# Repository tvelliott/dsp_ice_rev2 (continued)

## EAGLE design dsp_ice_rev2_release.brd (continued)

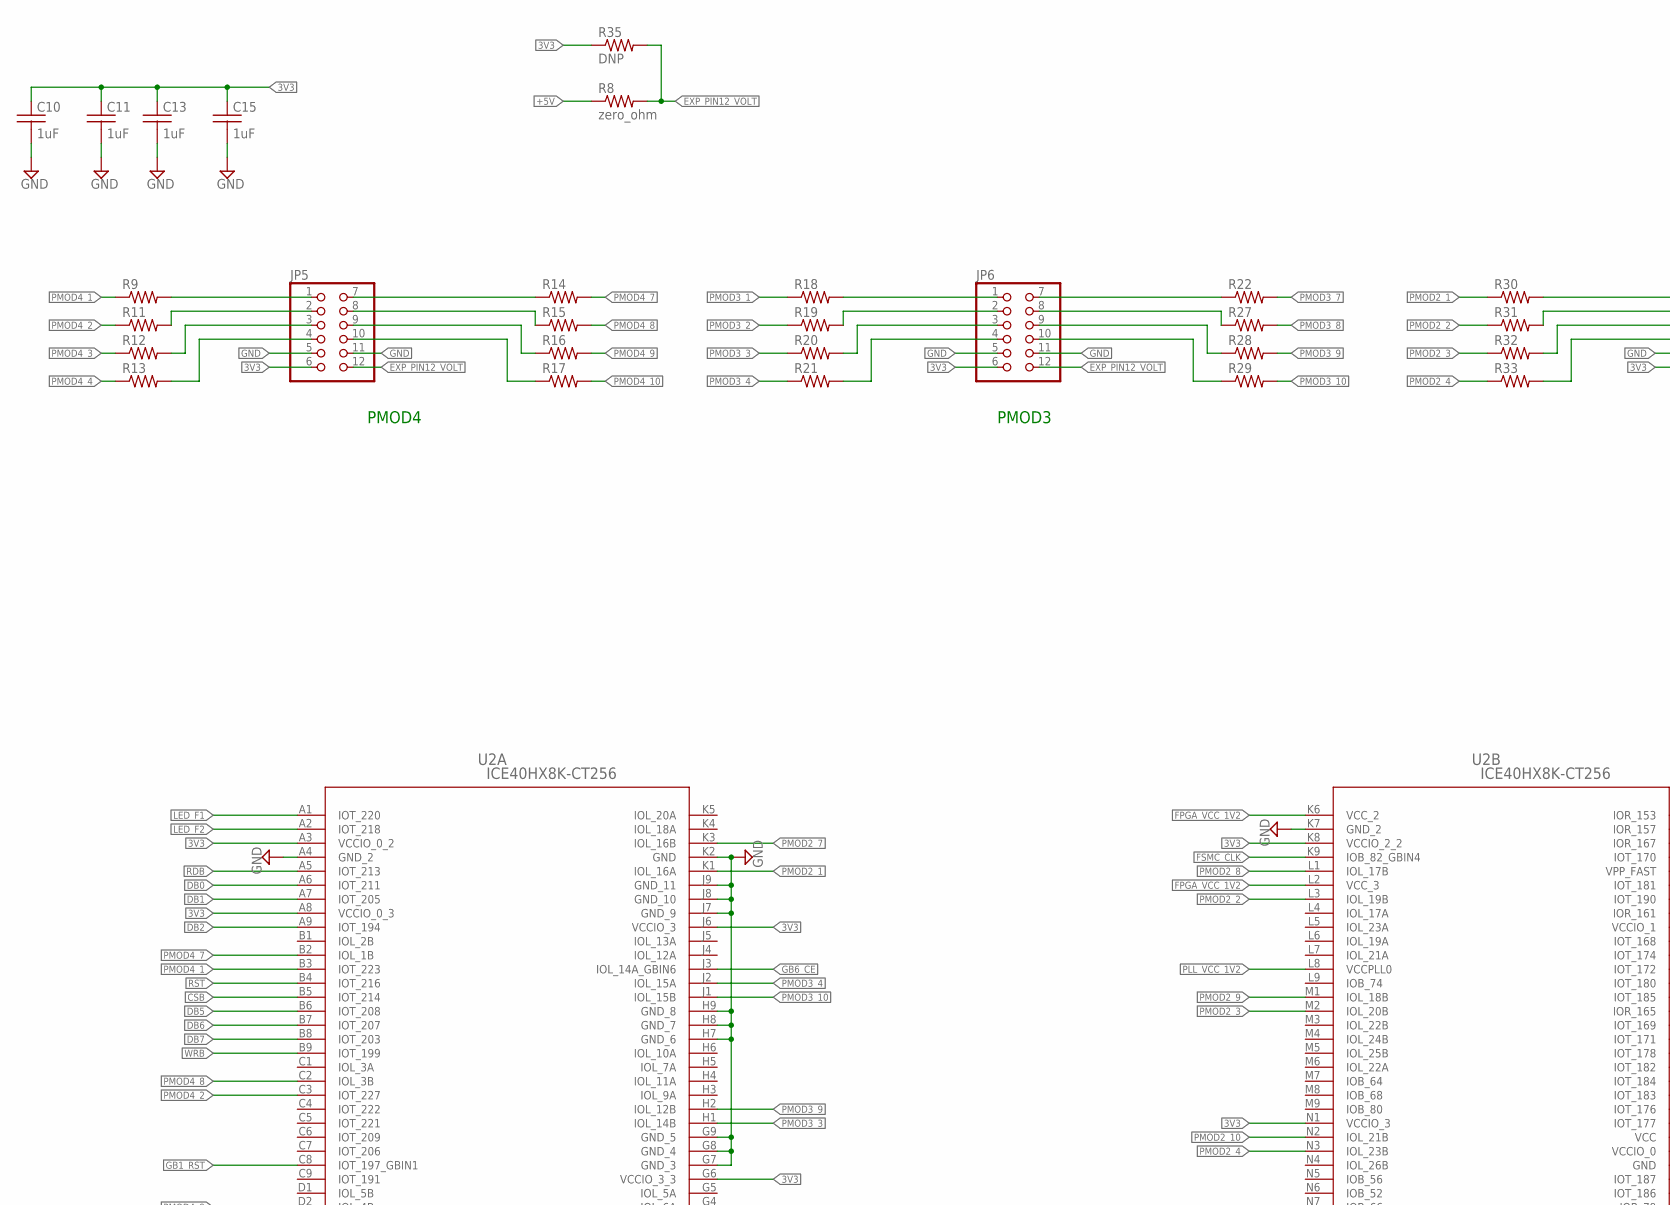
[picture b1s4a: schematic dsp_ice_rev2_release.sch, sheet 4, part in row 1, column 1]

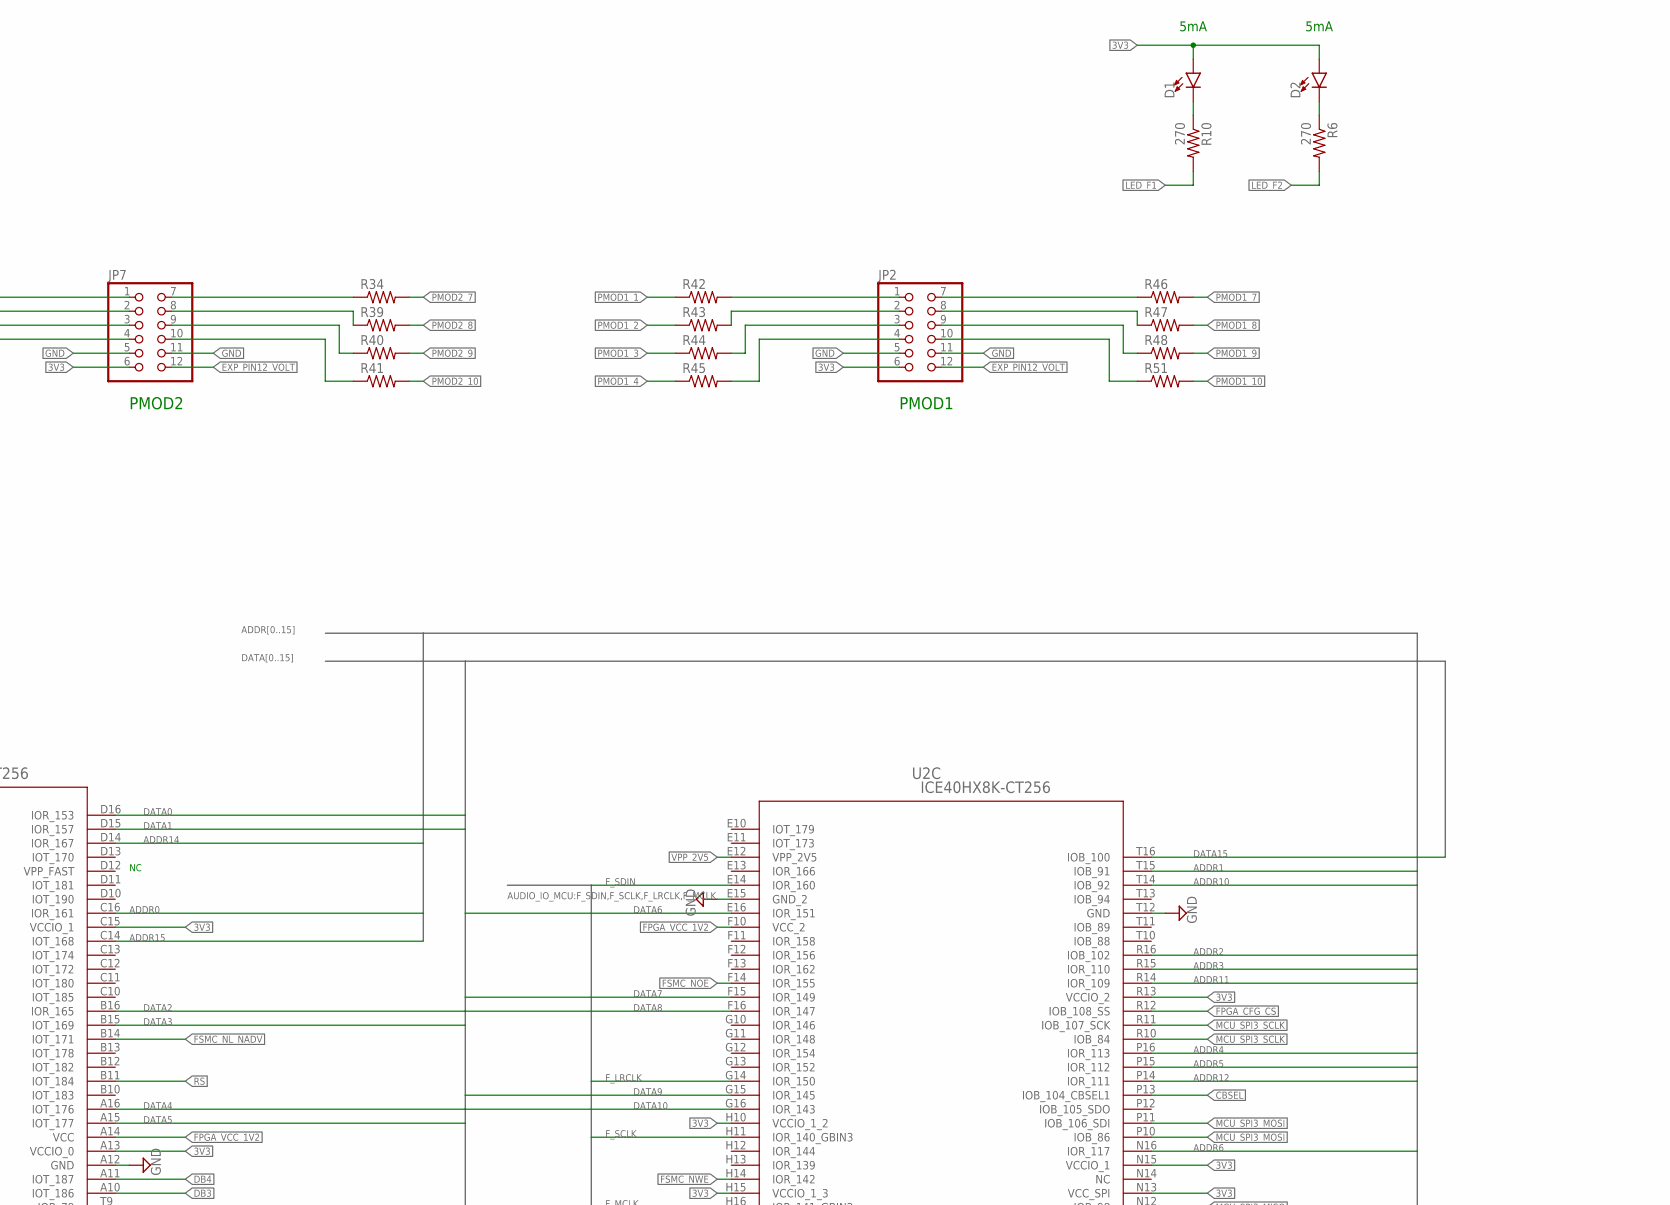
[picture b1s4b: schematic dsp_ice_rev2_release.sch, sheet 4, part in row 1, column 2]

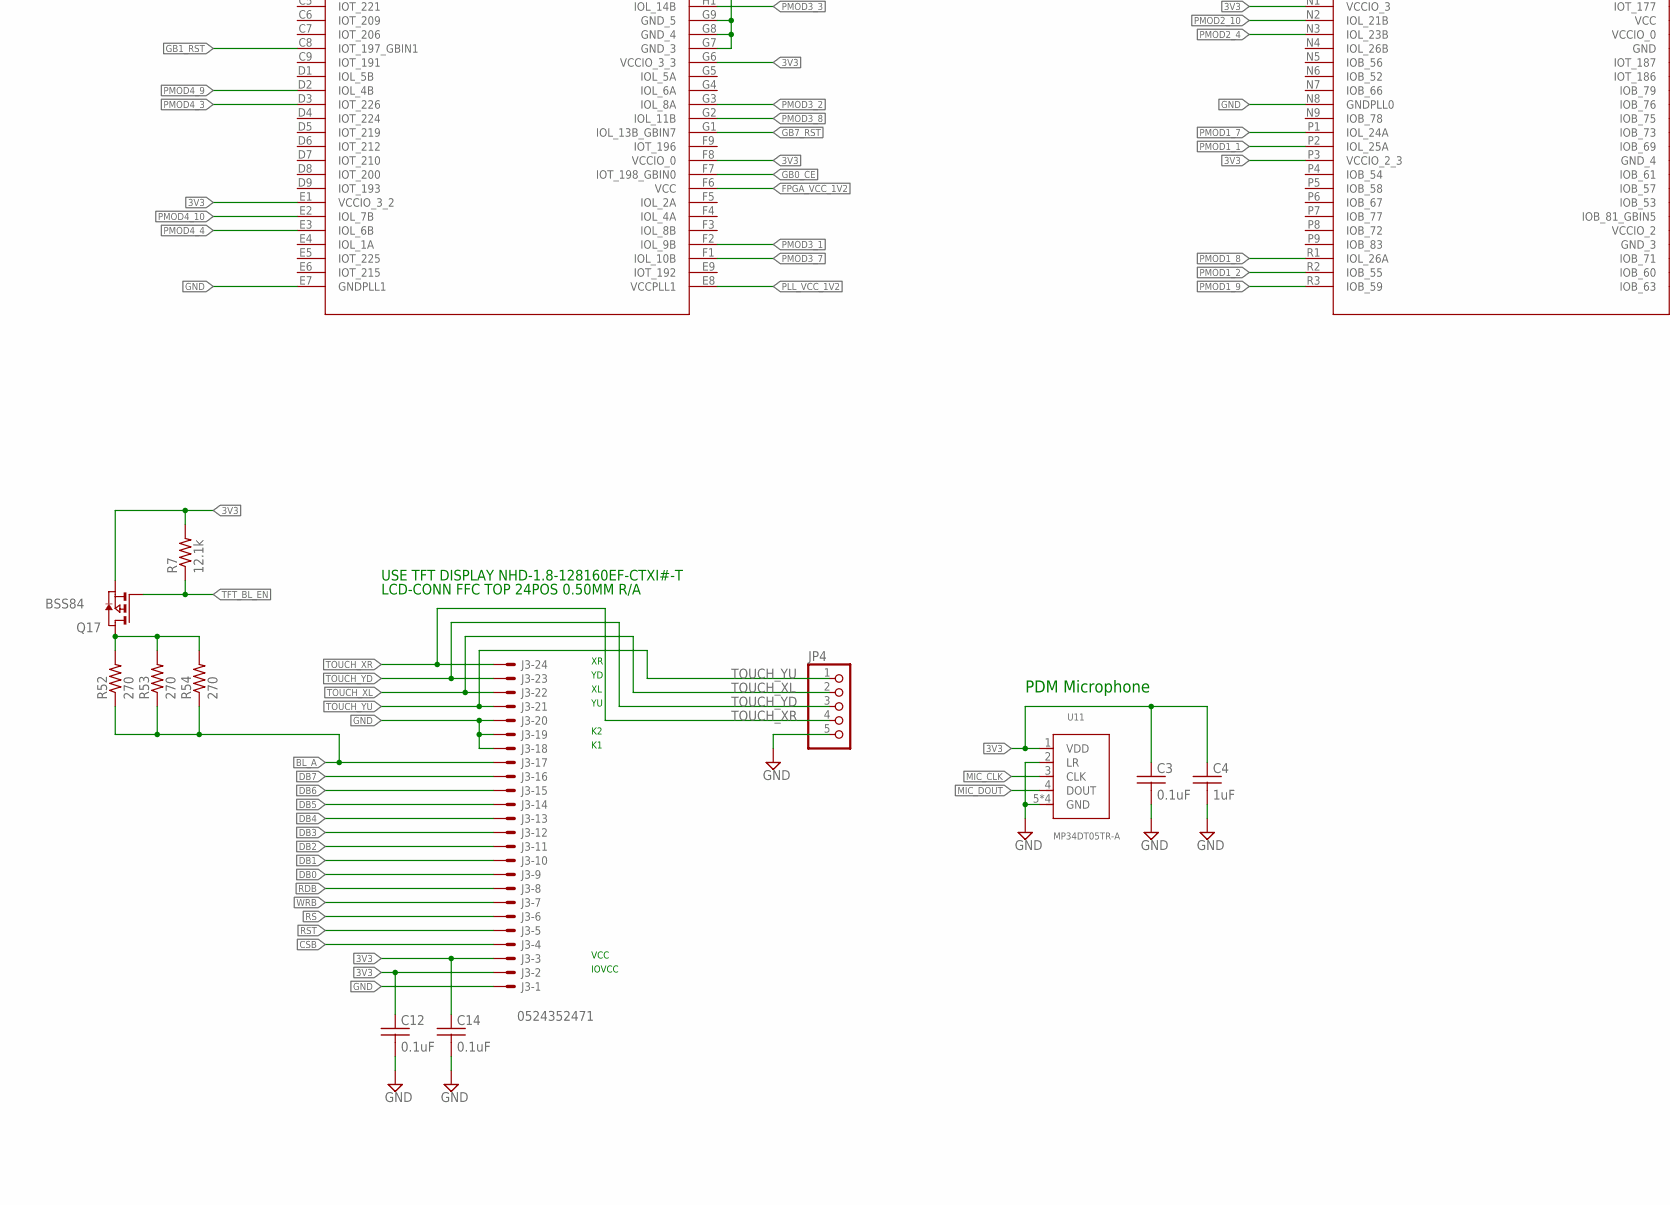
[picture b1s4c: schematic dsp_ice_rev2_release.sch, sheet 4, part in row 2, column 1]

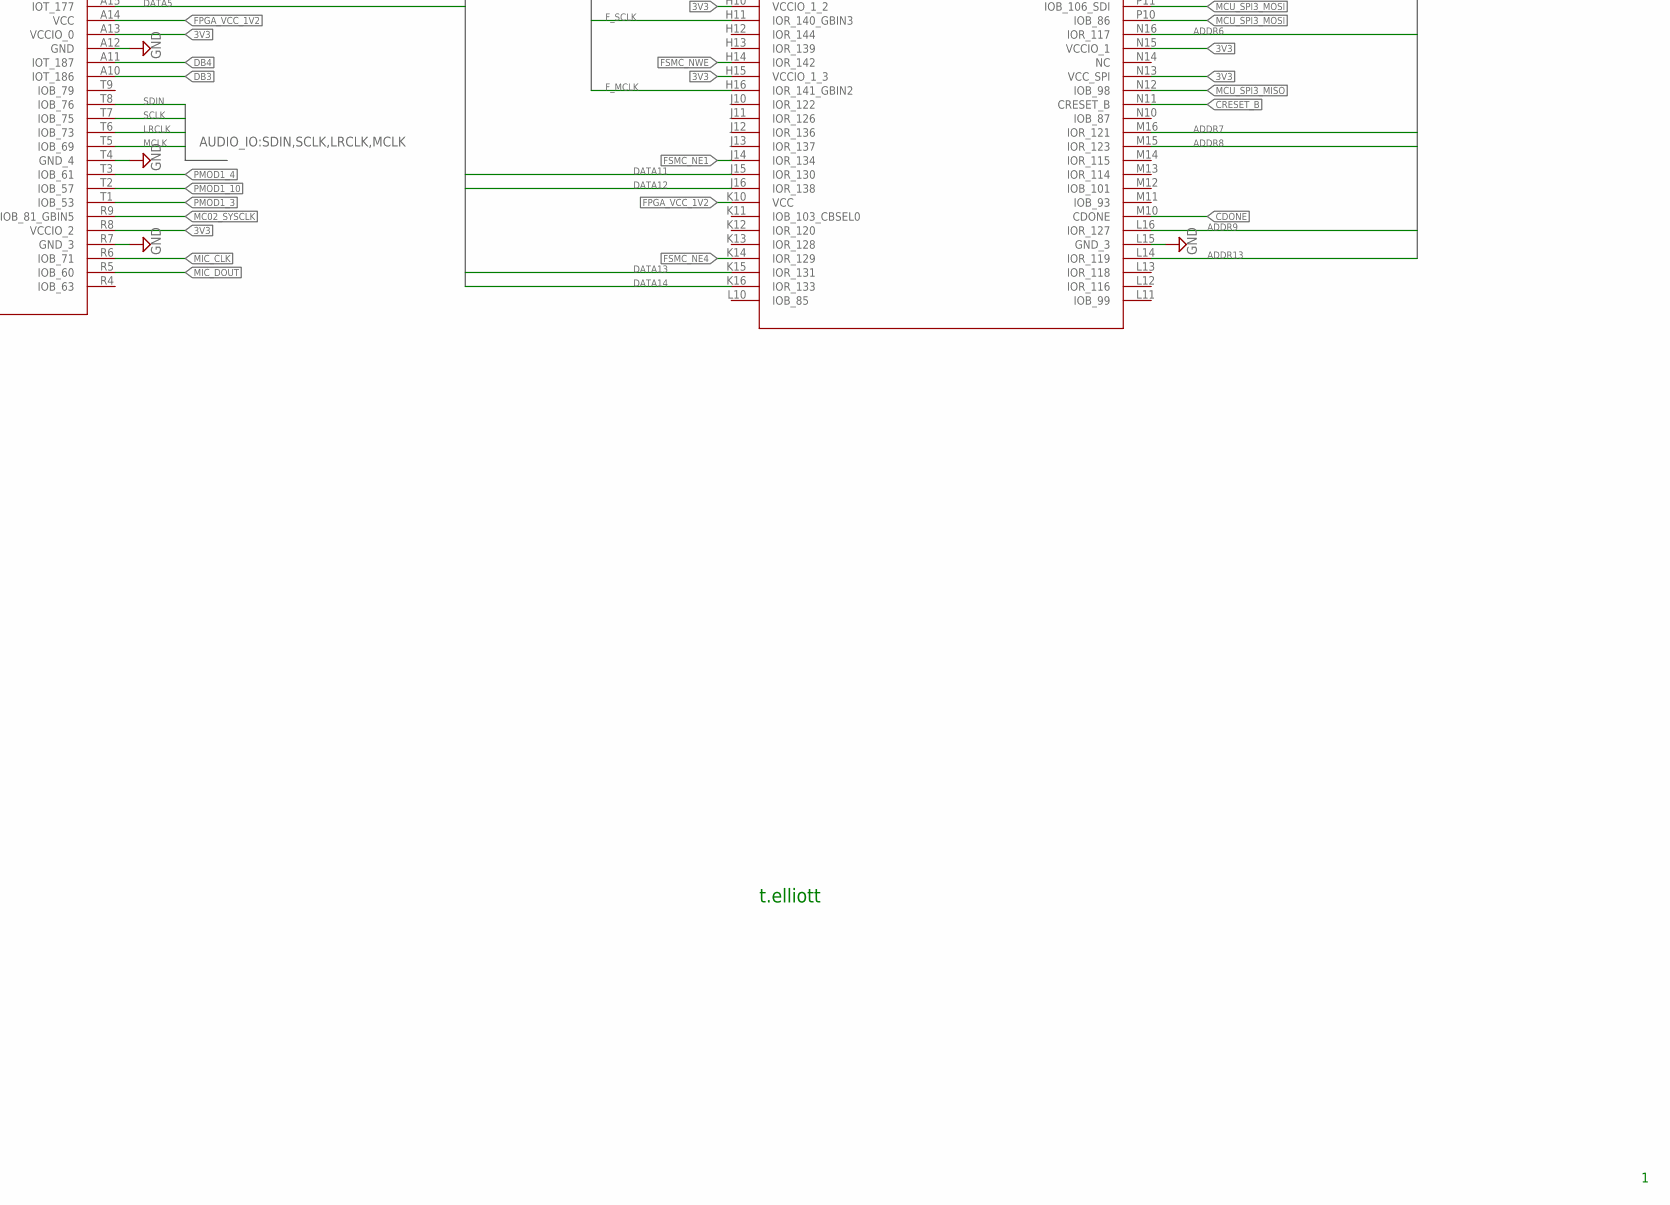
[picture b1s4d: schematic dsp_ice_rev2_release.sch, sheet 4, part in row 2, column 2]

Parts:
C3, C12, C14: 0.1uF; C0603
C4, C10, C11, C13, C15: 1uF; C0603
D1, D2: LED1206; LED-1206
J3: 0524352471; 52745-2490
JP2, JP5, JP6, JP7: PINHD-2X6; 2X06
JP4: PINHD-1X5; 1X05
Q17: BSS84; SOT23_BSS84_PACKAGE
R6, R10, R52, R53, R54: 270; R0603
R7: 12.1k; R0603
R8: zero_ohm; R1206W
R9, R11, R12, R13, R14, R15, R16, R17, R18, R19, R20, R21, R22, R27, R28, R29, R30, R31, R32, R33, R34, R39, R40, R41, R42, R43, R44, R45, R46, R47, R48, R51: 10; R0603
R35: DNP; R1206W
U2: ICE40HX8K-CT256; CABGA256
U11: MP34DT05TR-A; HCLGA5P-3X4X1MM

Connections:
3V3: C3.1, C4.1, C10.1, C11.1, C12.1, C13.1, C14.1, C15.1, D1.A, D2.A, J3.2, J3.3, JP2.6 (11), JP5.6 (11), JP6.6 (11), JP7.6 (11), Q17.2 (S), R7.2, R35.1, U2.A3 (VCCIO_0_2), U2.A8 (VCCIO_0_3), U2.A13 (VCCIO_0), U2.C15 (VCCIO_1), U2.E1 (VCCIO_3_2), U2.F8 (VCCIO_0), U2.G6 (VCCIO_3_3), U2.H10 (VCCIO_1_2), U2.H15 (VCCIO_1_3), U2.J6 (VCCIO_3), U2.K8 (VCCIO_2_2), U2.N1 (VCCIO_3), U2.N13 (VCC_SPI), U2.N15 (VCCIO_1), U2.P3 (VCCIO_2_3), U2.R8 (VCCIO_2), U2.R13 (VCCIO_2), U11.1 (VDD); also elsewhere on the board
+5V: R8.1; also elsewhere on the board
ADDR0: U2.C16 (IOR_161); also elsewhere on the board
ADDR1: U2.T15 (IOB_91); also elsewhere on the board
ADDR2: U2.R16 (IOB_102); also elsewhere on the board
ADDR3: U2.R15 (IOR_110); also elsewhere on the board
ADDR4: U2.P16 (IOR_113); also elsewhere on the board
ADDR5: U2.P15 (IOR_112); also elsewhere on the board
ADDR6: U2.N16 (IOR_117); also elsewhere on the board
ADDR7: U2.M16 (IOR_121); also elsewhere on the board
ADDR8: U2.M15 (IOR_123); also elsewhere on the board
ADDR9: U2.L16 (IOR_127); also elsewhere on the board
ADDR10: U2.T14 (IOB_92); also elsewhere on the board
ADDR11: U2.R14 (IOR_109); also elsewhere on the board
ADDR12: U2.P14 (IOR_111); also elsewhere on the board
ADDR13: U2.L14 (IOR_119); also elsewhere on the board
ADDR14: U2.D14 (IOR_167); also elsewhere on the board
ADDR15: U2.C14 (IOT_168); also elsewhere on the board
BL_A: J3.17, R52.1, R53.1, R54.1
CBSEL: U2.P13 (IOB_104_CBSEL1); also elsewhere on the board
CDONE: U2.M10 (CDONE); also elsewhere on the board
CRESET_B: U2.N11 (CRESET_B); also elsewhere on the board
CSB: J3.4, U2.B5 (IOT_214)
DATA0: U2.D16 (IOR_153); also elsewhere on the board
DATA1: U2.D15 (IOR_157); also elsewhere on the board
DATA2: U2.B16 (IOR_165); also elsewhere on the board
DATA3: U2.B15 (IOT_169); also elsewhere on the board
DATA4: U2.A16 (IOT_176); also elsewhere on the board
DATA5: U2.A15 (IOT_177); also elsewhere on the board
DATA6: U2.E16 (IOR_151); also elsewhere on the board
DATA7: U2.F15 (IOR_149); also elsewhere on the board
DATA8: U2.F16 (IOR_147); also elsewhere on the board
DATA9: U2.G15 (IOR_145); also elsewhere on the board
DATA10: U2.G16 (IOR_143); also elsewhere on the board
DATA11: U2.J15 (IOR_130); also elsewhere on the board
DATA12: U2.J16 (IOR_138); also elsewhere on the board
DATA13: U2.K15 (IOR_131); also elsewhere on the board
DATA14: U2.K16 (IOR_133); also elsewhere on the board
DATA15: U2.T16 (IOB_100); also elsewhere on the board
DB0: J3.9, U2.A6 (IOT_211)
DB1: J3.10, U2.A7 (IOT_205)
DB2: J3.11, U2.A9 (IOT_194)
DB3: J3.12, U2.A10 (IOT_186)
DB4: J3.13, U2.A11 (IOT_187)
DB5: J3.14, U2.B6 (IOT_208)
DB6: J3.15, U2.B7 (IOT_207)
DB7: J3.16, U2.B8 (IOT_203)
EXP_PIN12_VOLT: JP2.12, JP5.12, JP6.12, JP7.12, R8.2, R35.2
FPGA_CFG_CS: U2.R12 (IOB_108_SS); also elsewhere on the board
FPGA_VCC_1V2: U2.A14 (VCC), U2.F6 (VCC), U2.F10 (VCC_2), U2.K6 (VCC_2), U2.K10 (VCC), U2.L2 (VCC_3); also elsewhere on the board
FSMC_CLK: U2.K9 (IOB_82_GBIN4); also elsewhere on the board
FSMC_NE1: U2.J14 (IOR_134); also elsewhere on the board
FSMC_NE4: U2.K14 (IOR_129); also elsewhere on the board
FSMC_NL_NADV: U2.B14 (IOT_171); also elsewhere on the board
FSMC_NOE: U2.F14 (IOR_155); also elsewhere on the board
FSMC_NWE: U2.H14 (IOR_142); also elsewhere on the board
F_LRCLK: U2.G14 (IOR_150); also elsewhere on the board
F_MCLK: U2.H16 (IOR_141_GBIN2); also elsewhere on the board
F_SCLK: U2.H11 (IOR_140_GBIN3); also elsewhere on the board
F_SDIN: U2.E14 (IOR_160); also elsewhere on the board
GB0_CE: U2.F7 (IOT_198_GBIN0)
GB1_RST: U2.C8 (IOT_197_GBIN1)
GB6_CE: U2.J3 (IOL_14A_GBIN6)
GB7_RST: U2.G1 (IOL_13B_GBIN7)
GND: C3.2, C4.2, C10.2, C11.2, C12.2, C13.2, C14.2, C15.2, J3.1, J3.18, J3.19, J3.20, JP2.5 (9), JP2.11 (10), JP4.5, JP5.5 (9), JP5.11 (10), JP6.5 (9), JP6.11 (10), JP7.5 (9), JP7.11 (10), U2.A4 (GND_2), U2.A12 (GND), U2.E7 (GNDPLL1), U2.E15 (GND_2), U2.G7 (GND_3), U2.G8 (GND_4), U2.G9 (GND_5), U2.H7 (GND_6), U2.H8 (GND_7), U2.H9 (GND_8), U2.J7 (GND_9), U2.J8 (GND_10), U2.J9 (GND_11), U2.K2 (GND), U2.K7 (GND_2), U2.L15 (GND_3), U2.N8 (GNDPLL0), U2.R7 (GND_3), U2.T4 (GND_4), U2.T12 (GND), U11.2 (LR), U11.5 (GND), U11.6 (GND), U11.7 (GND), U11.8 (GND); also elsewhere on the board
LED_F1: R10.2, U2.A1 (IOT_220)
LED_F2: R6.2, U2.A2 (IOT_218)
LRCLK: U2.T6 (IOB_73); also elsewhere on the board
MC02_SYSCLK: U2.R9 (IOB_81_GBIN5); also elsewhere on the board
MCLK: U2.T5 (IOB_69); also elsewhere on the board
MCU_SPI3_MISO: U2.N12 (IOB_98); also elsewhere on the board
MCU_SPI3_MOSI: U2.P10 (IOB_86), U2.P11 (IOB_106_SDI); also elsewhere on the board
MCU_SPI3_SCLK: U2.R10 (IOB_84), U2.R11 (IOB_107_SCK); also elsewhere on the board
MIC_CLK: U2.R6 (IOB_71), U11.3 (CLK)
MIC_DOUT: U2.R5 (IOB_60), U11.4 (DOUT)
unnamed: Q17.3 (D), R52.2, R53.2, R54.2
unnamed: D1.C, R10.1
unnamed: D2.C, R6.1
unnamed: JP5.1, R9.2
unnamed: JP5.2 (3), R11.2
unnamed: JP5.3 (5), R12.2
unnamed: JP5.4 (7), R13.2
unnamed: JP5.10 (8), R17.1
unnamed: JP5.9 (6), R16.1
unnamed: JP5.8 (4), R15.1
unnamed: JP5.7 (2), R14.1
unnamed: JP6.1, R18.2
unnamed: JP6.2 (3), R19.2
unnamed: JP6.3 (5), R20.2
unnamed: JP6.4 (7), R21.2
unnamed: JP6.7 (2), R22.1
unnamed: JP6.8 (4), R27.1
unnamed: JP6.9 (6), R28.1
unnamed: JP6.10 (8), R29.1
unnamed: JP7.1, R30.2
unnamed: JP7.2 (3), R31.2
unnamed: JP7.3 (5), R32.2
unnamed: JP7.4 (7), R33.2
unnamed: JP7.7 (2), R34.1
unnamed: JP7.8 (4), R39.1
unnamed: JP7.9 (6), R40.1
unnamed: JP7.10 (8), R41.1
unnamed: JP2.1, R42.2
unnamed: JP2.2 (3), R43.2
unnamed: JP2.3 (5), R44.2
unnamed: JP2.4 (7), R45.2
unnamed: JP2.7 (2), R46.1
unnamed: JP2.8 (4), R47.1
unnamed: JP2.9 (6), R48.1
unnamed: JP2.10 (8), R51.1
PLL_VCC_1V2: U2.E8 (VCCPLL1), U2.L8 (VCCPLL0); also elsewhere on the board
PMOD1_1: R42.1, U2.P2 (IOL_25A)
PMOD1_2: R43.1, U2.R2 (IOB_55)
PMOD1_3: R44.1, U2.T1 (IOB_53)
PMOD1_4: R45.1, U2.T3 (IOB_61)
PMOD1_7: R46.2, U2.P1 (IOL_24A)
PMOD1_8: R47.2, U2.R1 (IOL_26A)
PMOD1_9: R48.2, U2.R3 (IOB_59)
PMOD1_10: R51.2, U2.T2 (IOB_57)
PMOD2_1: R30.1, U2.K1 (IOL_16A)
PMOD2_2: R31.1, U2.L3 (IOL_19B)
PMOD2_3: R32.1, U2.M2 (IOL_20B)
PMOD2_4: R33.1, U2.N3 (IOL_23B)
PMOD2_7: R34.2, U2.K3 (IOL_16B)
PMOD2_8: R39.2, U2.L1 (IOL_17B)
PMOD2_9: R40.2, U2.M1 (IOL_18B)
PMOD2_10: R41.2, U2.N2 (IOL_21B)
PMOD3_1: R18.1, U2.F2 (IOL_9B)
PMOD3_2: R19.1, U2.G3 (IOL_8A)
PMOD3_3: R20.1, U2.H1 (IOL_14B)
PMOD3_4: R21.1, U2.J2 (IOL_15A)
PMOD3_7: R22.2, U2.F1 (IOL_10B)
PMOD3_8: R27.2, U2.G2 (IOL_11B)
PMOD3_9: R28.2, U2.H2 (IOL_12B)
PMOD3_10: R29.2, U2.J1 (IOL_15B)
PMOD4_1: R9.1, U2.B3 (IOT_223)
PMOD4_2: R11.1, U2.C3 (IOT_227)
PMOD4_3: R12.1, U2.D3 (IOT_226)
PMOD4_4: R13.1, U2.E3 (IOL_6B)
PMOD4_7: R14.2, U2.B2 (IOL_1B)
PMOD4_8: R15.2, U2.C2 (IOL_3B)
PMOD4_9: R16.2, U2.D2 (IOL_4B)
PMOD4_10: R17.2, U2.E2 (IOL_7B)
RDB: J3.8, U2.A5 (IOT_213)
RS: J3.6, U2.B11 (IOT_184)
RST: J3.5, U2.B4 (IOT_216)
SCLK: U2.T7 (IOB_75); also elsewhere on the board
SDIN: U2.T8 (IOB_76); also elsewhere on the board
TFT_BL_EN: Q17.1 (G), R7.1; also elsewhere on the board
TOUCH_XL: J3.22, JP4.2; also elsewhere on the board
TOUCH_XR: J3.24, JP4.4; also elsewhere on the board
TOUCH_YD: J3.23, JP4.3; also elsewhere on the board
TOUCH_YU: J3.21, JP4.1; also elsewhere on the board
VPP_2V5: U2.E12 (VPP_2V5); also elsewhere on the board
VPP_FAST: U2.D12 (VPP_FAST)
WRB: J3.7, U2.B9 (IOT_199)

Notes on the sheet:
5mA
PMOD4
PMOD3
PMOD2
PMOD1
t.elliott
LCD-CONN FFC TOP 24POS 0.50MM R/A
USE TFT DISPLAY NHD-1.8-128160EF-CTXI#-T
PDM Microphone
VCC
IOVCC

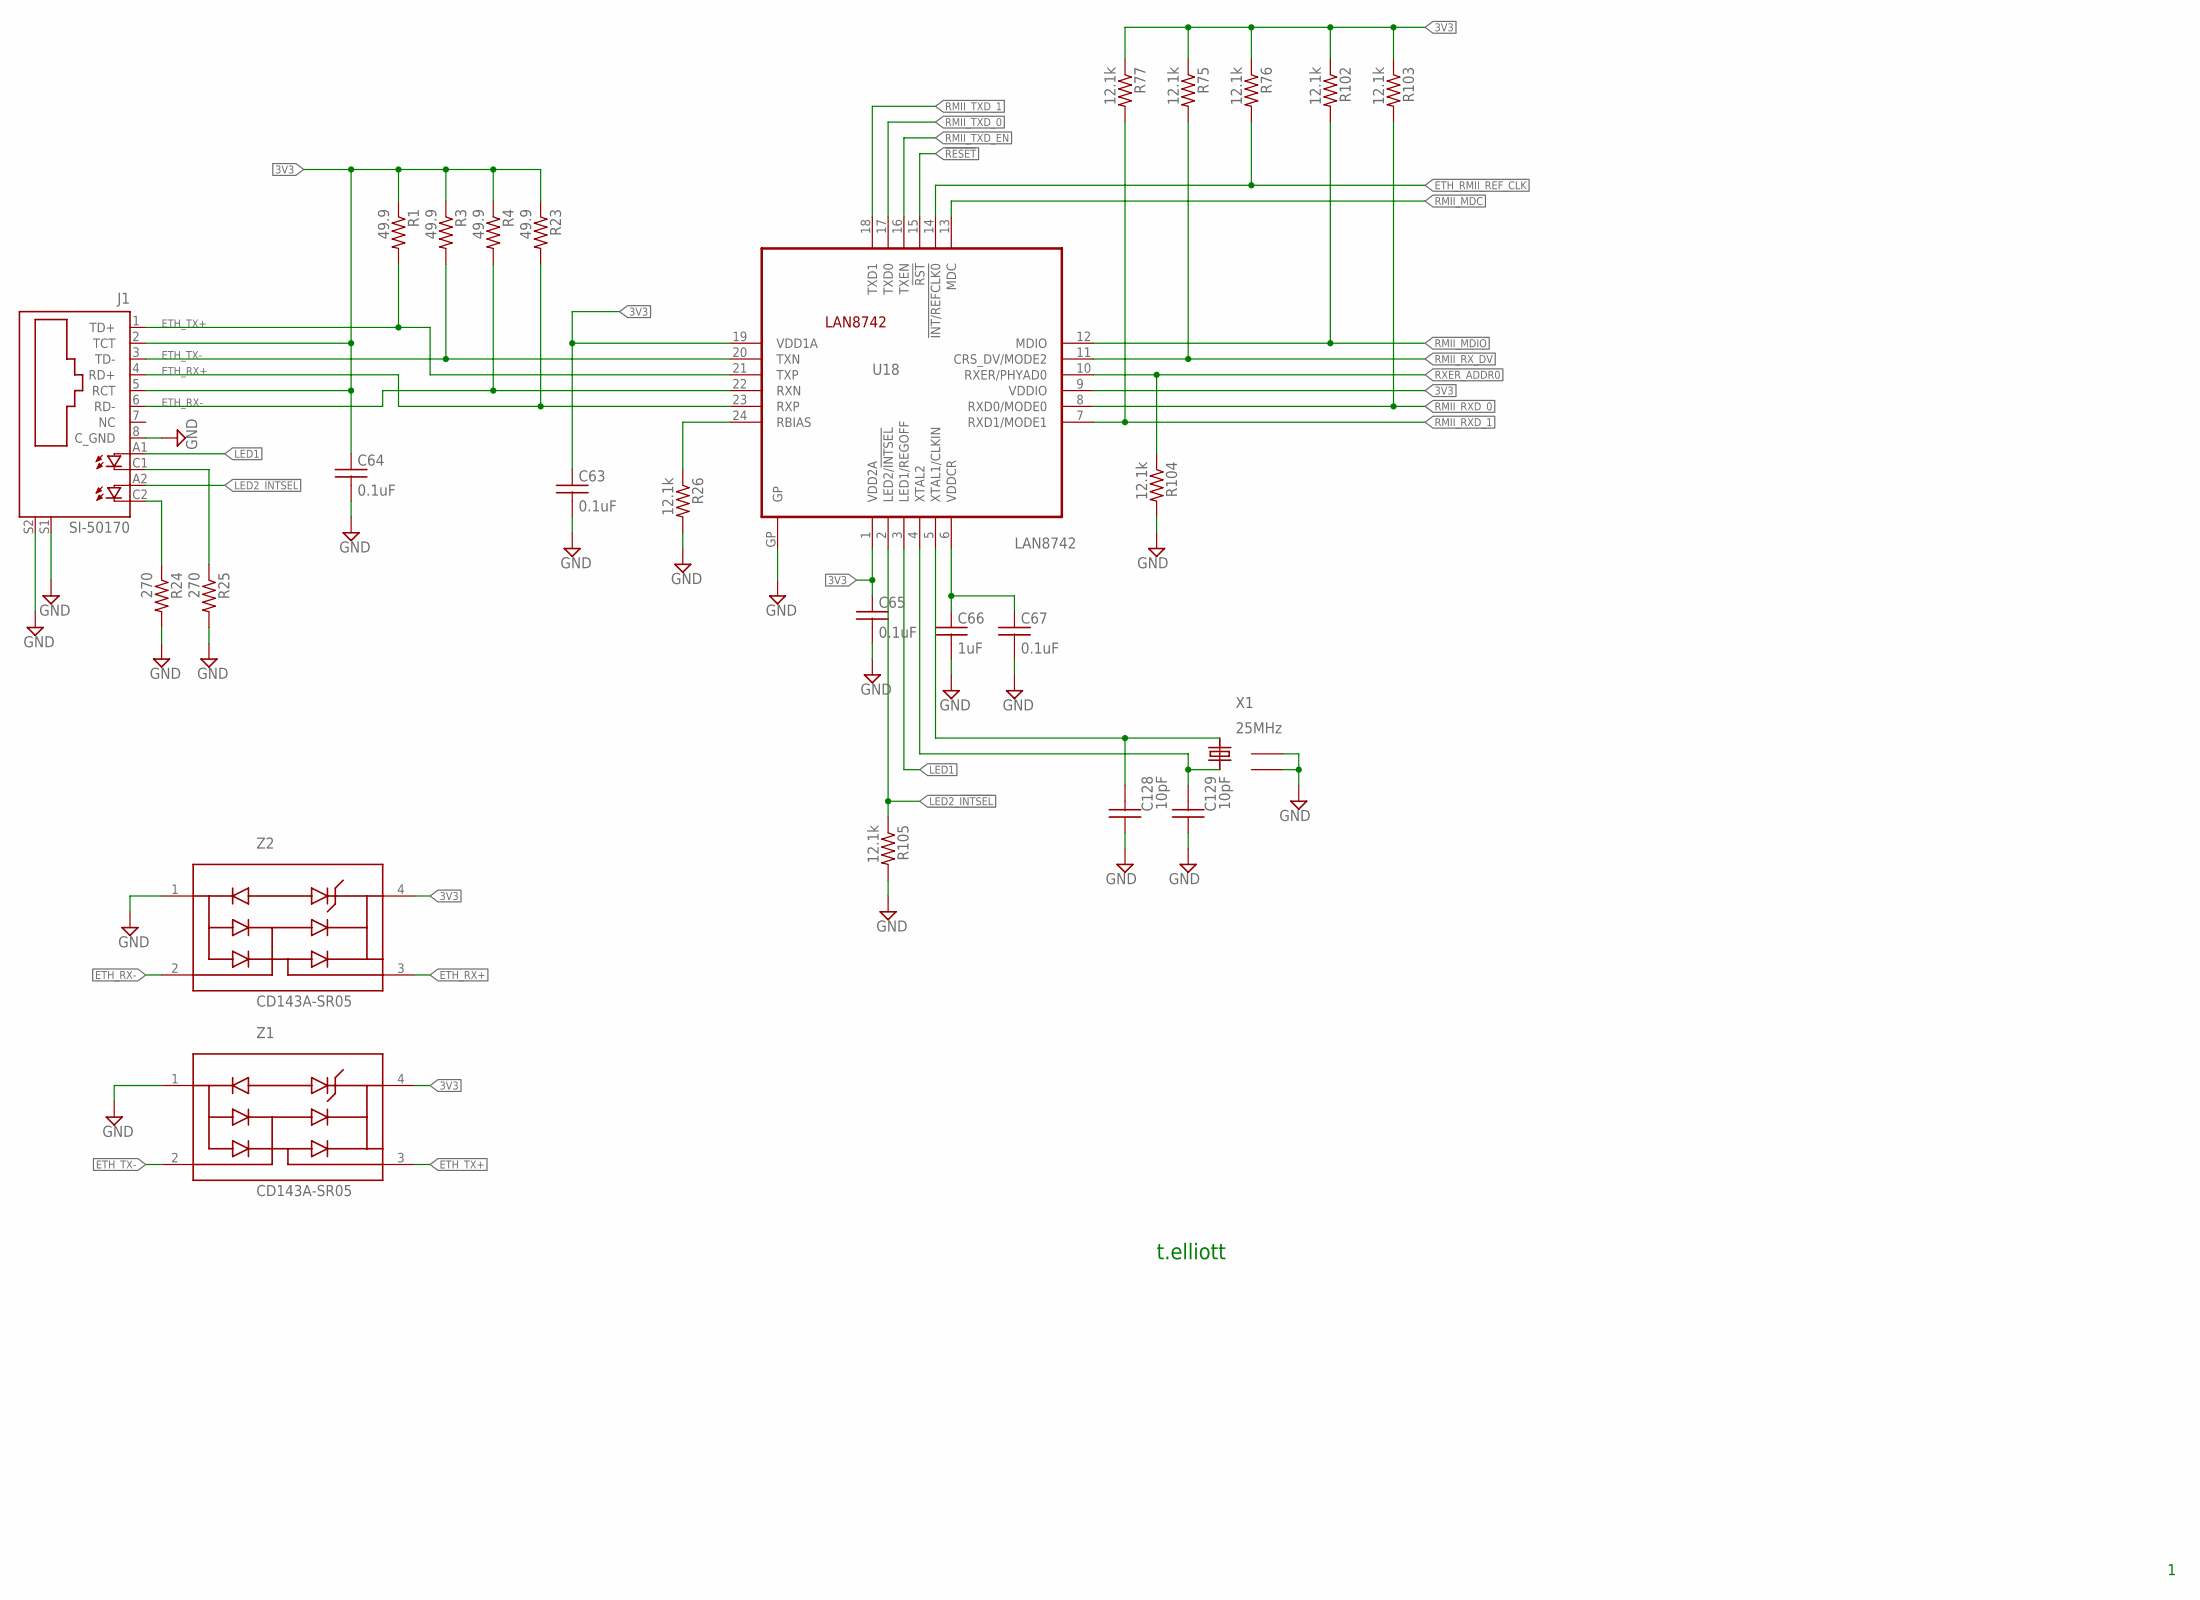
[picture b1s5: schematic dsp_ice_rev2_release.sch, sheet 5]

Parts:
C63, C64, C65, C67: 0.1uF; C0603
C66: 1uF; C0603
C128, C129: 10pF; C0402
J1: SI-50170
R1, R3, R4, R23: 49.9; R0603
R24, R25: 270; R0603
R26, R75, R76, R77, R102, R103, R104, R105: 12.1k; R0603
U18: LAN8742; QFN-24
X1: 25MHz; ECS-250-20-30B-DU_CRYSTAL
Z1, Z2: CD143A-SR05; SR2.8.TCT_1PRIMARY

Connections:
3V3: C63.1, C64.1, C65.1, J1.2 (TCT), J1.5 (RCT), R1.1, R3.1, R4.1, R23.1, R75.1, R76.1, R77.1, R102.1, R103.1, U18.1 (VDD2A), U18.9 (VDDIO), U18.19 (VDD1A), Z1.4 (REF), Z2.4 (REF); also elsewhere on the board
!RESET: U18.15 (!RST); also elsewhere on the board
ETH_RMII_REF_CLK: R76.2, U18.14 (!INT/REFCLK0); also elsewhere on the board
ETH_RX+: J1.4 (RD+), R23.2, U18.23 (RXP), Z2.3 (I/O)
ETH_RX-: J1.6 (RD-), R4.2, U18.22 (RXN), Z2.2 (I/O)
ETH_TX+: J1.1 (TD+), R1.2, U18.21 (TXP), Z1.3 (I/O)
ETH_TX-: J1.3 (TD-), R3.2, U18.20 (TXN), Z1.2 (I/O)
GND: C63.2, C64.2, C65.2, C66.2, C67.2, C128.1, C129.1, J1.8 (C_GND), J1.S1, J1.S2, R24.2, R25.2, R26.2, R104.2, R105.2, U18.GP, X1.GND@1 (1), X1.GND@2 (2), Z1.1 (GND), Z2.1 (GND); also elsewhere on the board
LED1: J1.A1 (A), U18.3 (LED1/REGOFF)
LED2_!INTSEL: J1.A2 (A1), R105.1, U18.2 (LED2/!INTSEL)
unnamed: R26.1, U18.24 (RBIAS)
unnamed: C66.1, C67.1, U18.6 (VDDCR)
unnamed: J1.C2 (C1), R24.1
unnamed: J1.C1 (C), R25.1
unnamed: C129.2, U18.4 (XTAL2), X1.3
unnamed: C128.2, U18.5 (XTAL1/CLKIN), X1.1
RMII_MDC: U18.13 (MDC); also elsewhere on the board
RMII_MDIO: R102.2, U18.12 (MDIO); also elsewhere on the board
RMII_RXD_0: R103.2, U18.8 (RXD0/MODE0); also elsewhere on the board
RMII_RXD_1: R77.2, U18.7 (RXD1/MODE1); also elsewhere on the board
RMII_RX_DV: R75.2, U18.11 (CRS_DV/MODE2); also elsewhere on the board
RMII_TXD_0: U18.17 (TXD0); also elsewhere on the board
RMII_TXD_1: U18.18 (TXD1); also elsewhere on the board
RMII_TXD_EN: U18.16 (TXEN); also elsewhere on the board
RXER_ADDR0: R104.1, U18.10 (RXER/PHYAD0)

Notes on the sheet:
t.elliott

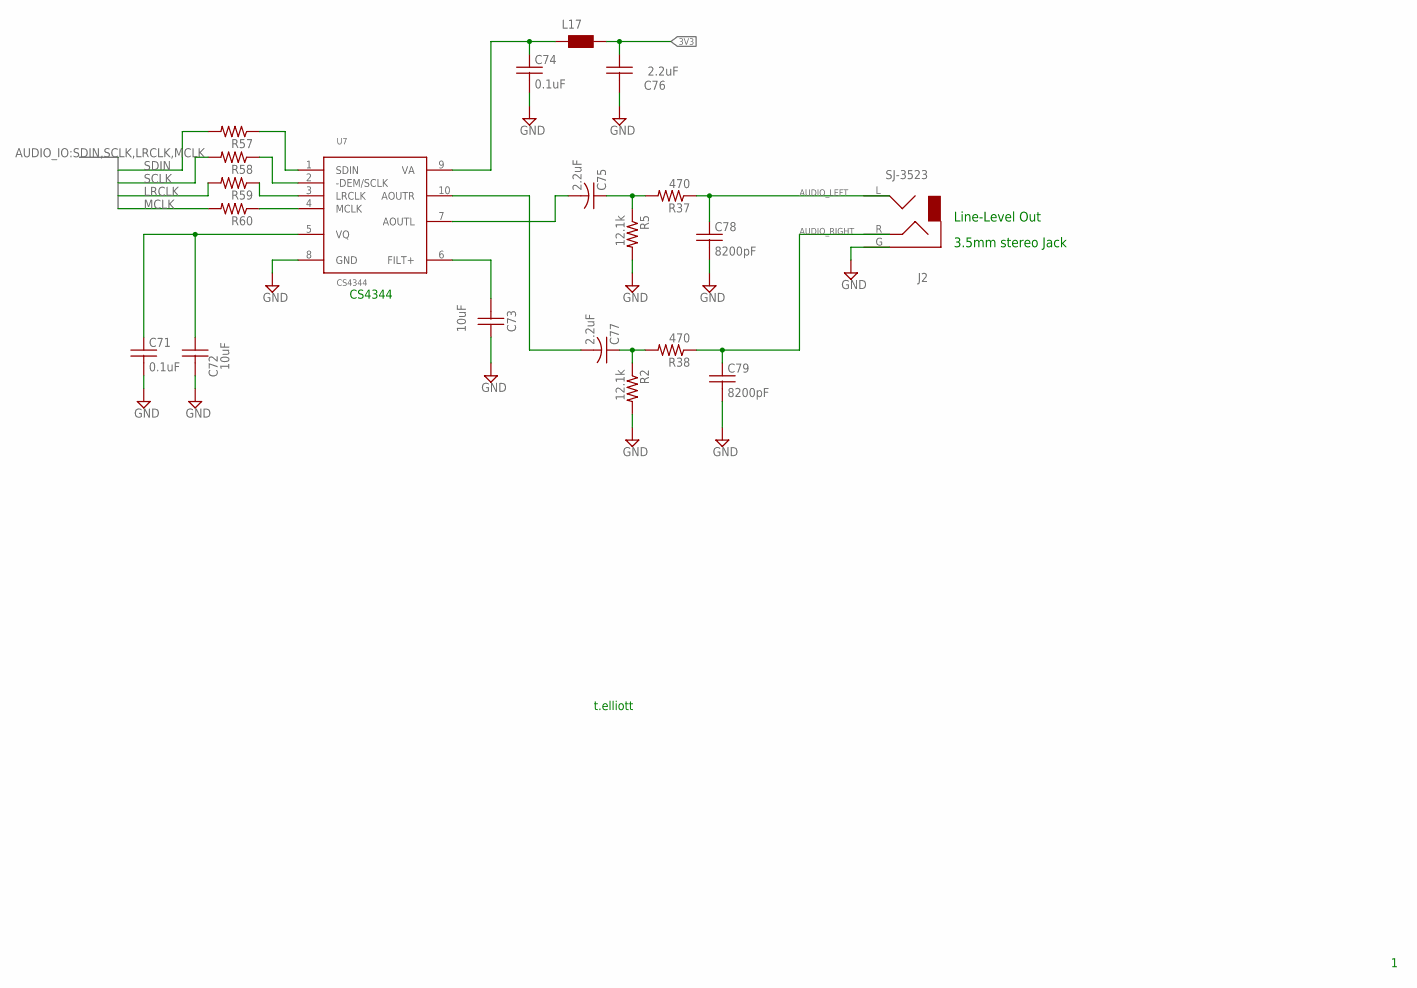
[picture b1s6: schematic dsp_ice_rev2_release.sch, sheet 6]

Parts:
C71, C74: 0.1uF; C0603
C72, C73: 10uF; C0805
C75, C76, C77: 2.2uF; C0805
C78, C79: 8200pF; C0603
J2: SJ-3523
L17: WE-CBF_0603; 0603
R2, R5: 12.1k; R0603
R37, R38, R57, R58, R59, R60: 470; R0402
U7: CS4344; MSOP10

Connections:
3V3: C76.1, L17.2; also elsewhere on the board
AUDIO_LEFT: C79.1, J2.R, R38.1
AUDIO_RIGHT: C78.1, J2.L, R37.1
GND: C71.2, C72.2, C73.1, C74.2, C76.2, C78.2, C79.2, J2.G, R2.2, R5.2, U7.8 (GND); also elsewhere on the board
LRCLK: R59.2; also elsewhere on the board
MCLK: R60.2; also elsewhere on the board
unnamed: C77.2, U7.10 (AOUTR)
unnamed: R60.1, U7.4 (MCLK)
unnamed: R59.1, U7.3 (LRCLK)
unnamed: R58.1, U7.2 (-DEM/SCLK)
unnamed: R57.1, U7.1 (SDIN)
unnamed: C73.2, U7.6 (FILT+)
unnamed: C71.1, C72.1, U7.5 (VQ)
unnamed: C75.2, U7.7 (AOUTL)
unnamed: C75.1, R5.1, R37.2
unnamed: C77.1, R2.1, R38.2
unnamed: C74.1, L17.1, U7.9 (VA)
SCLK: R58.2; also elsewhere on the board
SDIN: R57.2; also elsewhere on the board

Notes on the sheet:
t.elliott
CS4344
Line-Level Out
3.5mm stereo Jack
